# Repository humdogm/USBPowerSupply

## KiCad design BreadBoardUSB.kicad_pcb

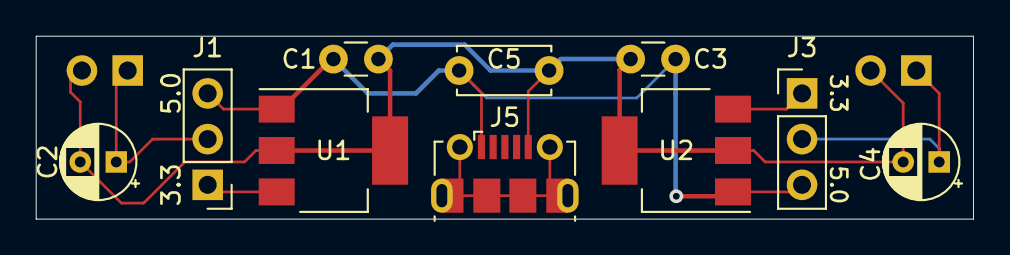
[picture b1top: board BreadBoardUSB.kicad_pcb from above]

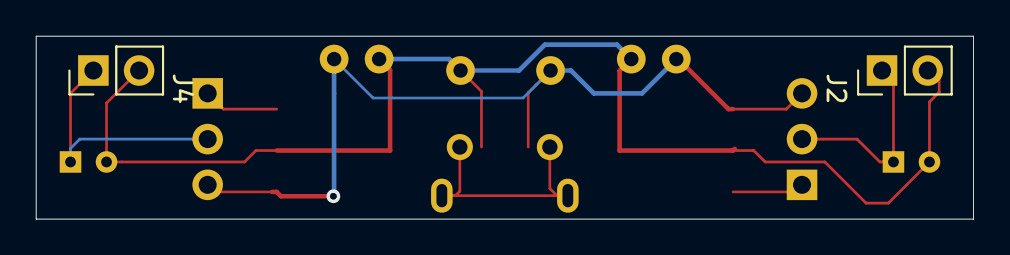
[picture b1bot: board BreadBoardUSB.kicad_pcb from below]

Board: 2 copper layers, 52.1 x 10.2 mm, 12 parts (2 on the bottom side), 6 nets.

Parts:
C1, C3: 0.1uF; C_Disc_D3.0mm_W1.6mm_P2.50mm
C2, C4: 10uF; CP_Radial_D4.0mm_P2.00mm
C5: 0.1uF; C_Disc_D5.0mm_W2.5mm_P5.00mm
J1, J3: Conn_01x03_Male; PinHeader_1x03_P2.54mm_Vertical
J2, J4: Conn_01x02_Male; PinHeader_1x02_P2.54mm_Vertical
J5: USB_B_Micro; USB_Micro-B_Molex-105017-0001
U1, U2: LM2937xMP; SOT-223-3_TabPin2

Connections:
GNDREF: C1.2, C2.2, C3.2, C4.2, C5.2, J2.2, J4.2, J5.5, U1.2, U2.2
unnamed: C2.1, J1.2, J2.1
unnamed: C4.1, J3.2, J4.1
unnamed: J1.1, U1.3
unnamed: J3.1, U2.3
VBUS: C1.1, C3.1, C5.1, J1.3, J3.3, J5.1, U1.1, U2.1

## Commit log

2021-10-19 Complete first iteration
